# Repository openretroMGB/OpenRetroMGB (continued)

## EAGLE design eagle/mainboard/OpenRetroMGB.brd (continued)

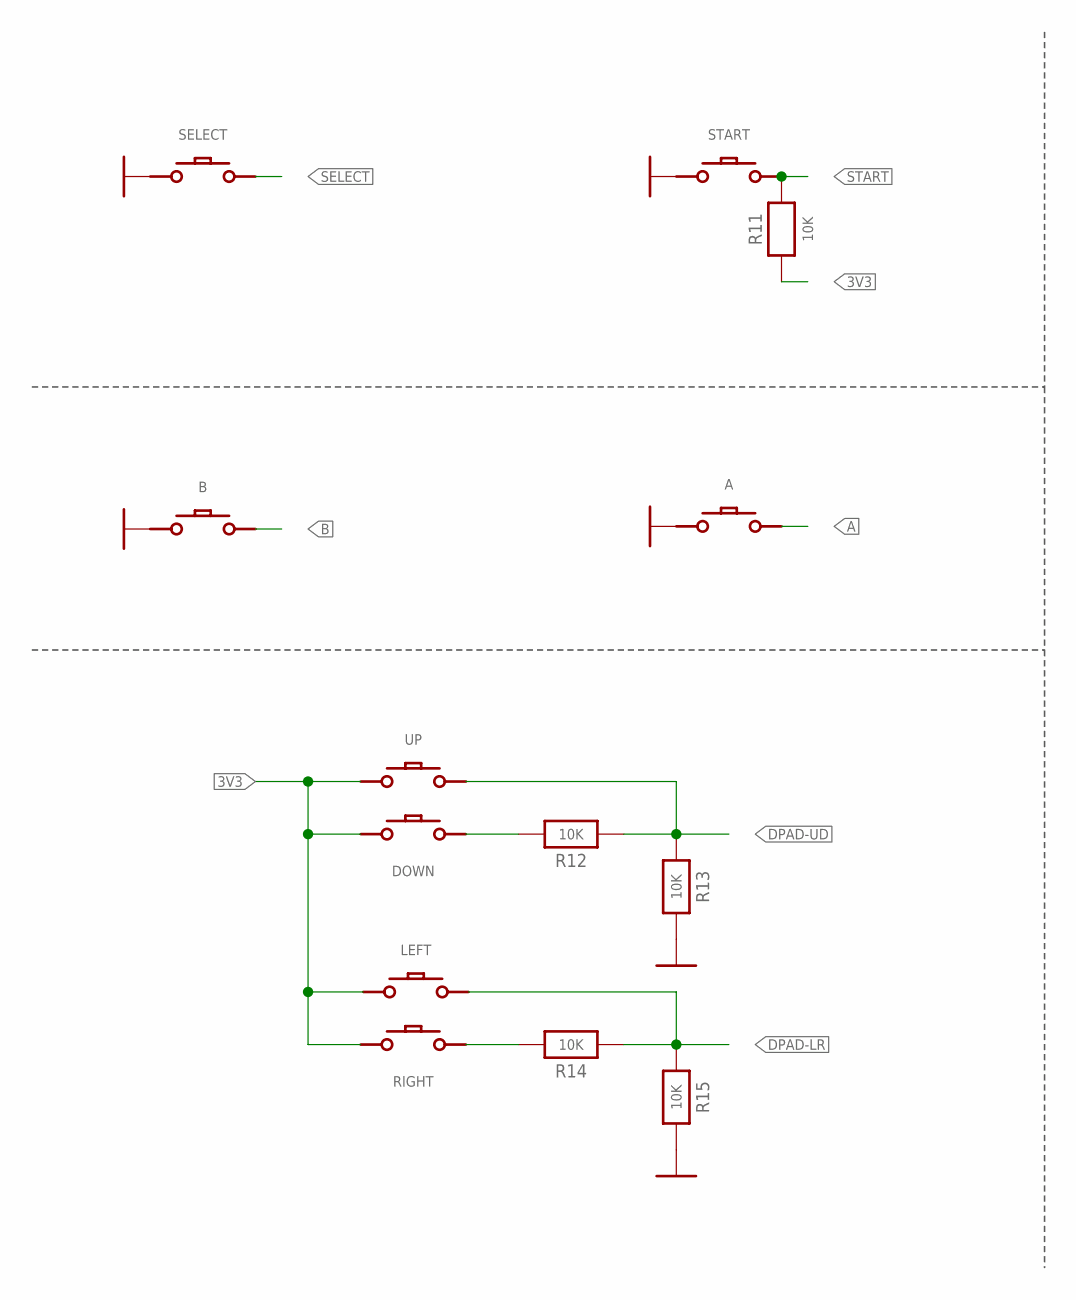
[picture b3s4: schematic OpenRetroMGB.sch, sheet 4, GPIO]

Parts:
A: CONDUCTIVE_BUTTONCONDUCTIVE_BUTTON_MGB; CONDUCTIVE_BUTTON_MGB
B: CONDUCTIVE_BUTTONCONDUCTIVE_BUTTON_MGB; CONDUCTIVE_BUTTON_MGB
DOWN: CONDUCTIVE_BUTTON; CONDUCTIVE_BUTTON_DIRECTIONAL
LEFT: CONDUCTIVE_BUTTON; CONDUCTIVE_BUTTON_DIRECTIONAL
R11, R12, R13, R14, R15: 10K; 0603-MINI; MPN ERJ-PA3J103V
RIGHT: CONDUCTIVE_BUTTON; CONDUCTIVE_BUTTON_DIRECTIONAL
SELECT: CONDUCTIVE_BUTTON_STARTSELECTCONDUCTIVE_BUTTON_TH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; CONDUCTIVE_BUTTON_THICK_STARTSELECT
START: CONDUCTIVE_BUTTON_STARTSELECTCONDUCTIVE_BUTTON_TH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; CONDUCTIVE_BUTTON_THICK_STARTSELECT
UP: CONDUCTIVE_BUTTON; CONDUCTIVE_BUTTON_DIRECTIONAL

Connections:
3V3: DOWN.P$GND, LEFT.P$GND, R11.1, RIGHT.P$GND, UP.P$GND; also elsewhere on the board
A: A.P$ACTIVE, A.P$ACTIVE1 (P$ACTIVE); also elsewhere on the board
B: B.P$ACTIVE, B.P$ACTIVE1 (P$ACTIVE); also elsewhere on the board
DOWN: DOWN.P$ACTIVE, R12.2
DPAD-LR: LEFT.P$ACTIVE, R14.1, R15.1; also elsewhere on the board
DPAD-UD: R12.1, R13.1, UP.P$ACTIVE; also elsewhere on the board
GND: A.P$GND, A.P$GND1 (P$GND), B.P$GND, B.P$GND1 (P$GND), R13.2, R15.2, SELECT.P$GND, SELECT.P$GND1 (P$GND), SELECT.P$GND2 (P$GND), SELECT.P$GND3 (P$GND), START.P$GND, START.P$GND1 (P$GND), START.P$GND2 (P$GND), START.P$GND3 (P$GND); also elsewhere on the board
RIGHT: R14.2, RIGHT.P$ACTIVE
SELECT: SELECT.P$ACTIVE, SELECT.P$ACTIVE1 (P$ACTIVE), SELECT.P$ACTIVE2 (P$ACTIVE), SELECT.P$ACTIVE3 (P$ACTIVE), SELECT.P$ACTIVE4 (P$ACTIVE), SELECT.P$ACTIVE5 (P$ACTIVE), SELECT.P$ACTIVE6 (P$ACTIVE); also elsewhere on the board
START: R11.2, START.P$ACTIVE, START.P$ACTIVE1 (P$ACTIVE), START.P$ACTIVE2 (P$ACTIVE), START.P$ACTIVE3 (P$ACTIVE), START.P$ACTIVE4 (P$ACTIVE), START.P$ACTIVE5 (P$ACTIVE), START.P$ACTIVE6 (P$ACTIVE); also elsewhere on the board

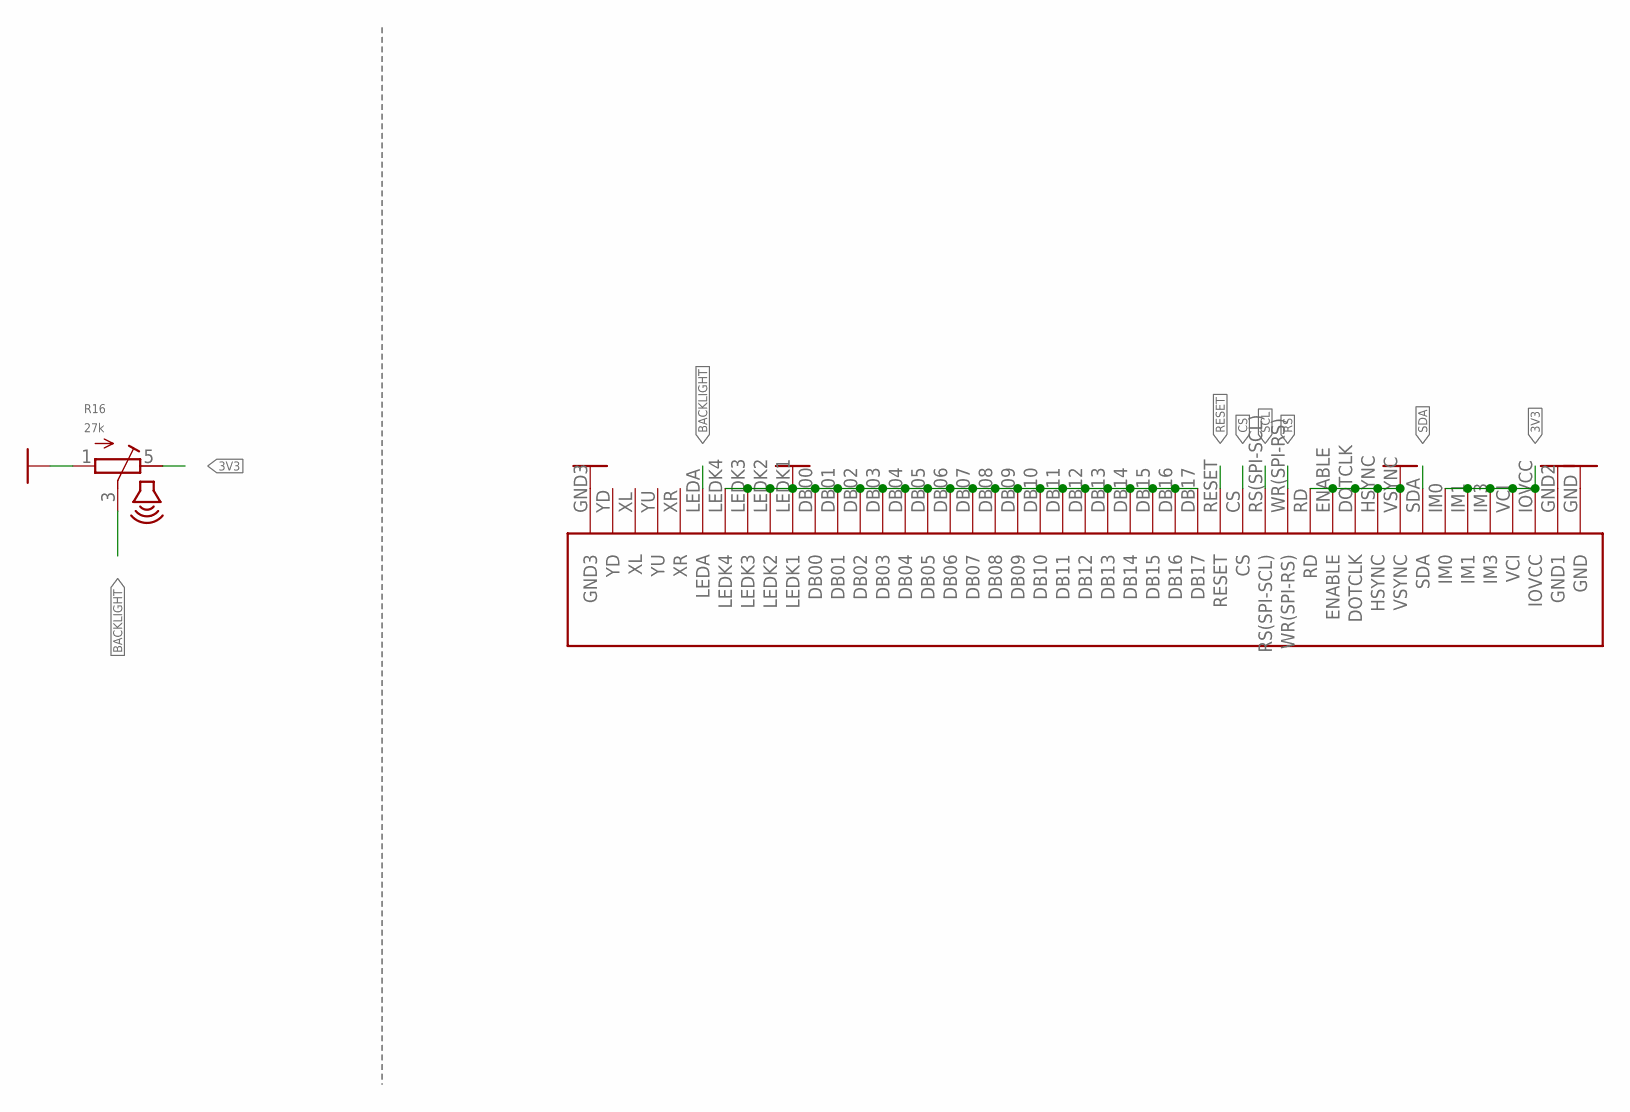
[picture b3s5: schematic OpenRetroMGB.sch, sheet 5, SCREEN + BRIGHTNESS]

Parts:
R16: 27k; THUMBWHEEL
U$11: KD026LQTMA008; MPN 0541324562

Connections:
3V3: R16.5 (E), U$11.IM0, U$11.IM1, U$11.IM3, U$11.IOVCC, U$11.VCI; also elsewhere on the board
BACKLIGHT: R16.3 (S), U$11.LEDA
CS: U$11.CS; also elsewhere on the board
GND: R16.1 (A), U$11.DB00, U$11.DB01, U$11.DB02, U$11.DB03, U$11.DB04, U$11.DB05, U$11.DB06, U$11.DB07, U$11.DB08, U$11.DB09, U$11.DB10, U$11.DB11, U$11.DB12, U$11.DB13, U$11.DB14, U$11.DB15, U$11.DB16, U$11.DB17, U$11.DOTCLK, U$11.ENABLE, U$11.GND, U$11.GND2 (GND1), U$11.GND3, U$11.HSYNC, U$11.LEDK1, U$11.LEDK2, U$11.LEDK3, U$11.LEDK4, U$11.RD, U$11.VSYNC; also elsewhere on the board
RESET: U$11.RESET; also elsewhere on the board
RS: U$11.WR(SPI-RS); also elsewhere on the board
SCL: U$11.RS(SPI-SCL); also elsewhere on the board
SDA: U$11.SDA; also elsewhere on the board

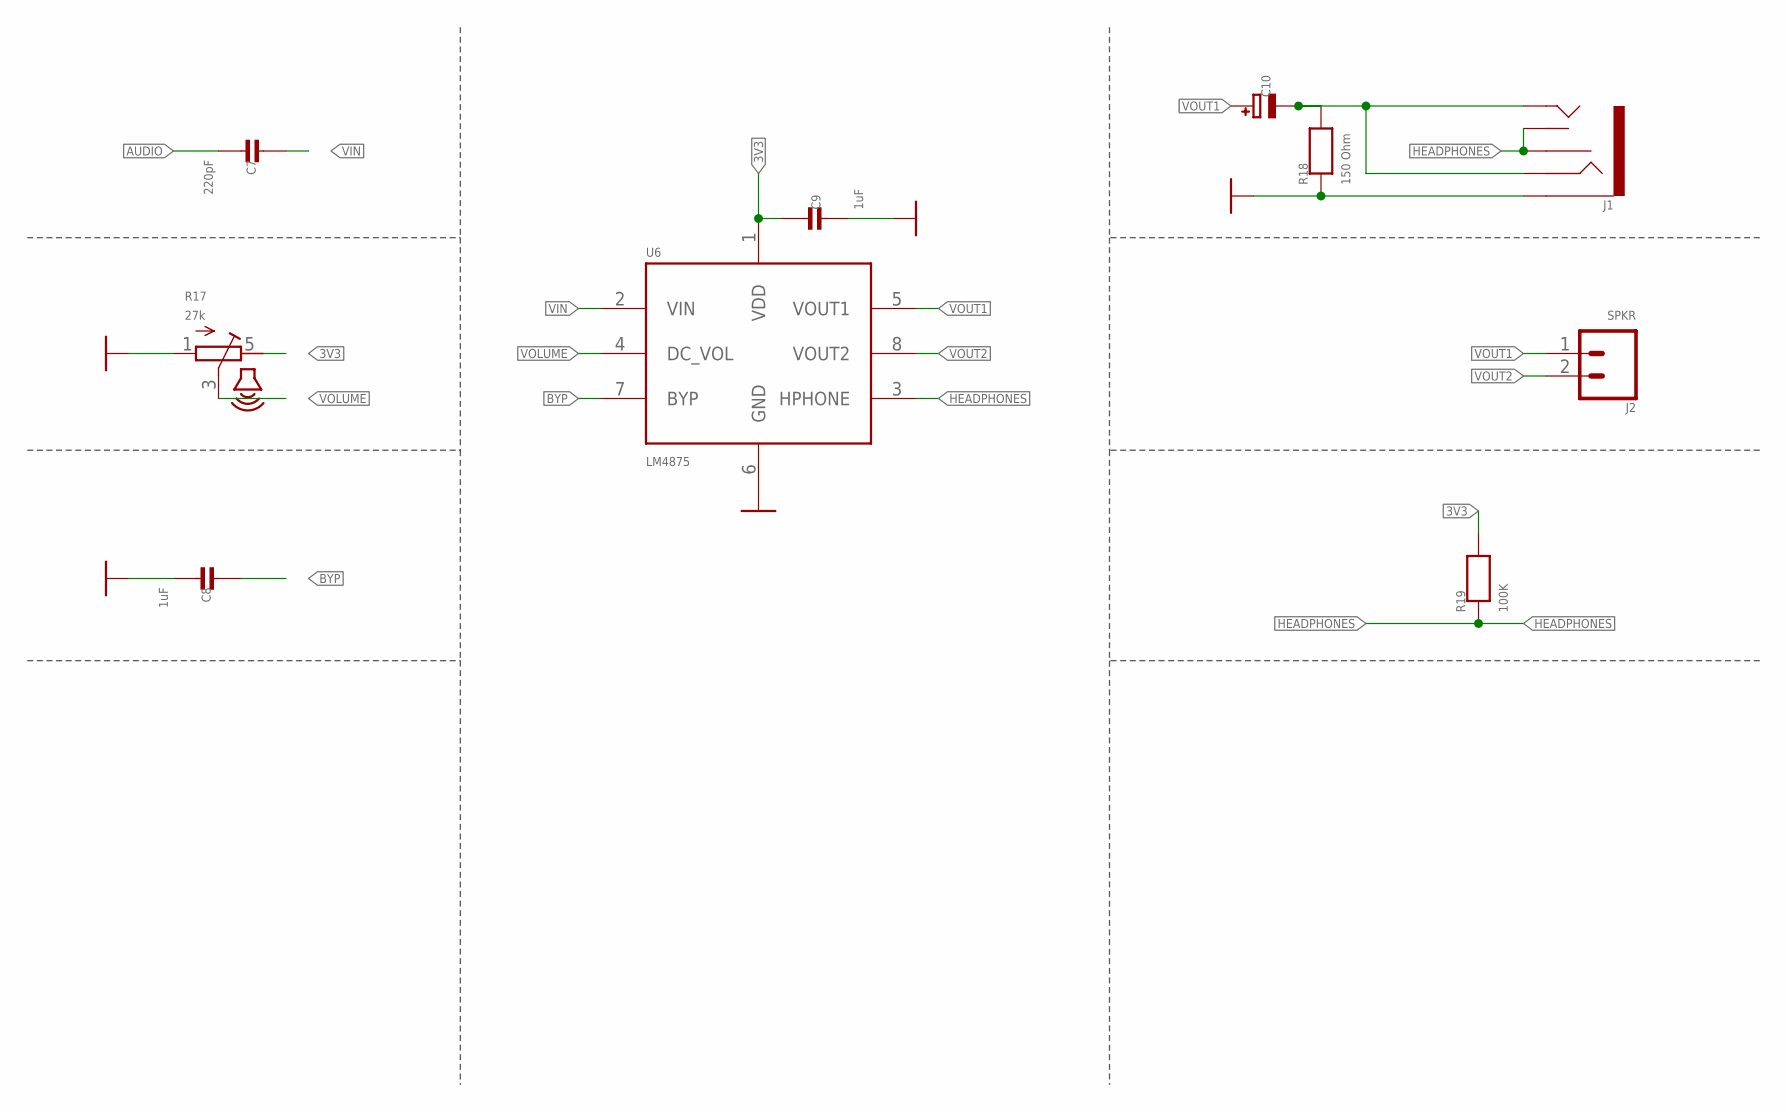
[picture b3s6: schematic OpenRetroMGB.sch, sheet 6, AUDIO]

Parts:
C7: 220pF; 0603-MINI-CAP; MPN CL10C221JB8NNNC
C8, C9: 1uF; 0603-MINI-CAP; MPN CL10A105KP8NNNC
C10: 100uF; EIA3216-18/A-W; MPN F930J107KAA
J1: AUDIO_JACK_3.5MM_KIT; AUDIO-JACK-KIT; MPN SJ1-3525NG-GR
J2: SPKR; 1X02
R17: 27k; THUMBWHEEL
R18: 150 Ohm; 0603-MINI; MPN ERJ-PA3J151V
R19: 100K; 0603-MINI; MPN ERJ-PA3J104V
U6: LM4875; SOIC8; MPN LM4875MX/NOPB

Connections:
3V3: C9.1, R17.5 (E), R19.2, U6.1 (VDD); also elsewhere on the board
AUDIO: C7.2; also elsewhere on the board
BYP: C8.1, U6.7 (BYP)
GND: C8.2, C9.2, J1.SLEEVE, R17.1 (A), R18.1, U6.6 (GND); also elsewhere on the board
HEADPHONES: J1.RSH, J1.TSH, R19.1, U6.3 (HPHONE)
VIN: C7.1, U6.2 (VIN)
VIN1: C10.-, J1.RING, J1.TIP, R18.2
VOLUME: R17.3 (S), U6.4 (DC_VOL)
VOUT1: C10.+, J2.1, U6.5 (VOUT1)
VOUT2: J2.2, U6.8 (VOUT2)

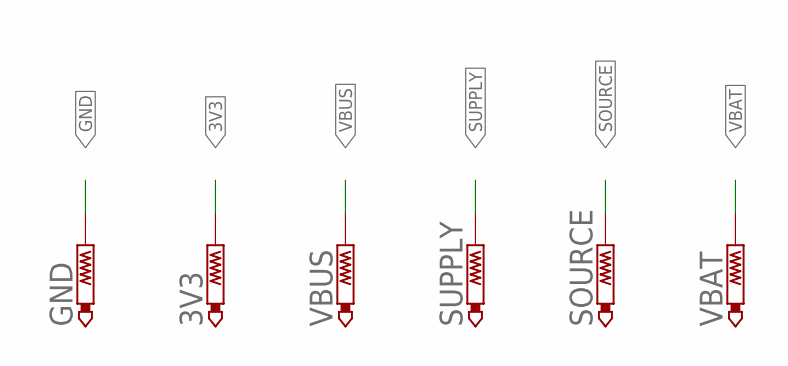
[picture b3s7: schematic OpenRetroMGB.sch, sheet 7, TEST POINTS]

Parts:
3V3: TESTPADTP18R; TESTPAD
GND: GND; TESTPAD
SOURCE: TESTPADTP18R; TESTPAD
SUPPLY: TESTPADTP18R; TESTPAD
VBAT: TESTPADTP18R; TESTPAD
VBUS: TESTPADTP18R; TESTPAD

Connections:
3V3: 3V3.TP; also elsewhere on the board
GND: GND.TP; also elsewhere on the board
SOURCE: SOURCE.TP; also elsewhere on the board
SUPPLY: SUPPLY.TP; also elsewhere on the board
VBAT: VBAT.TP; also elsewhere on the board
VBUS: VBUS.TP; also elsewhere on the board

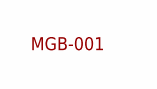
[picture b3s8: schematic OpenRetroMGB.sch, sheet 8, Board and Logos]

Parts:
U$17: MGB-001

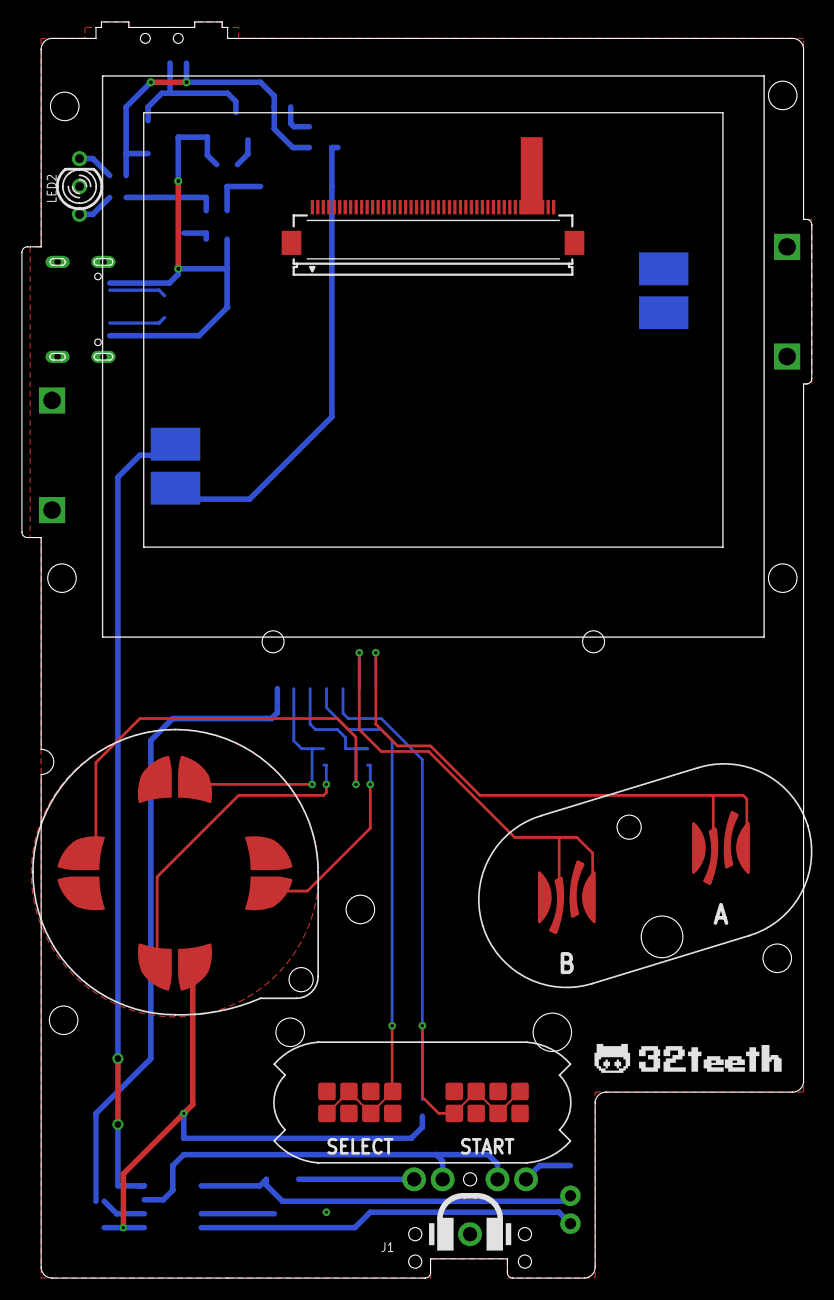
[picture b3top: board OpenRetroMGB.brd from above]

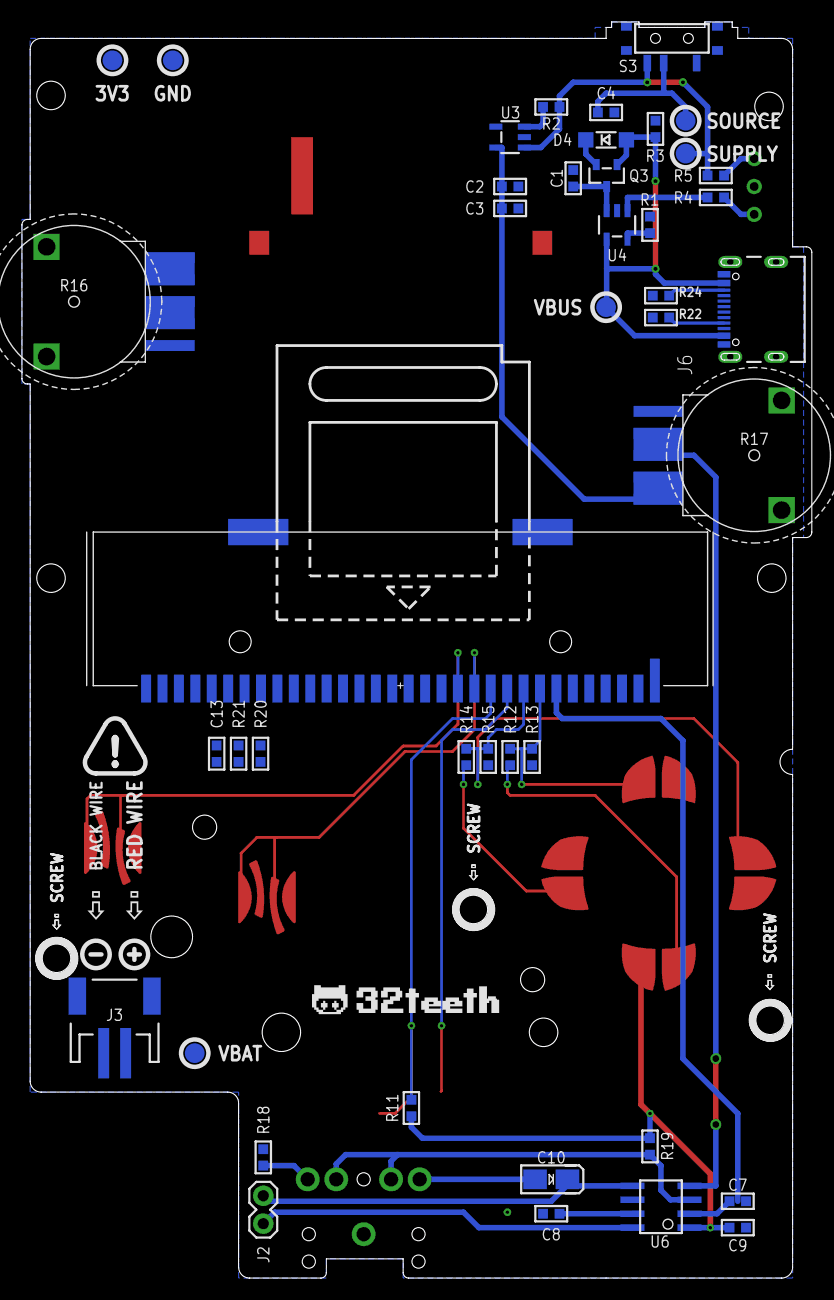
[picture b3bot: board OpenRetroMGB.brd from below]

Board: 2 copper layers, 72.0 x 114.5 mm, 55 parts (43 on the bottom side), 36 nets.

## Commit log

2023-04-28 Initial Commit - The one that started it all
2023-04-29 feat: README and assets
2023-04-29 fix: ignore files
2023-04-30 feat: new repo asnd org
2023-05-01 Update FUNDING.yml
    add this org
2023-05-02 feat: added slotted mainboard for passthru lcd ribbon
2023-05-02 feat: images
2023-05-03 feat: added BOM for mainboard
2023-05-04 feat: added bill of materials
2023-05-04 fix: README
2023-05-04 fix: naming for bom and gerbers
2023-05-04 feat: USB C - Lines
2023-05-05 feat: new splash
2023-05-05 fix updated README
2023-05-05 update: gallery README
2023-05-11 feat: Atmega32u4
2023-05-12 feat: Atmega32u4 image and BOM
2023-05-12 feat: retro esp32 image
2023-05-14 feat: added links to 32u4 bom
2023-05-18 feat: ten years
2023-05-18 feat: readme update
2023-05-19 feat: added slim csv bom for mainboard
2023-05-19 feat: removed unsourcable parts from seeed studio mainboard
2023-05-19 feat: added interactive PCB for mainboard
2023-05-19 feat: added dxf files
2023-05-19 feat: added interactive bom for retroesp32 cart
2023-05-22 feat: official open shource hardware announcement
2023-05-26 feat: rotate lcd
2023-05-26 feat: pre commit hook for cleanup
2023-06-09 feat: quick asset update
2023-06-14 feat: release Atmega32U4
2023-06-14 feat: 32u4 full release
2023-06-14 feat: update JST to Molex connector
2023-06-27 feat: updated U$11 component
2023-06-28 feat: prod run
2023-07-02 feat: release cartridge OSH
2023-07-03 feat: update Atmega32u4
2023-07-09 feat: update board
2023-07-10 feat: tighter d-pad
2023-07-27 feat: update USB and VCC lines on ATMega
2023-07-30 feat: redesign ATmega cartridge
